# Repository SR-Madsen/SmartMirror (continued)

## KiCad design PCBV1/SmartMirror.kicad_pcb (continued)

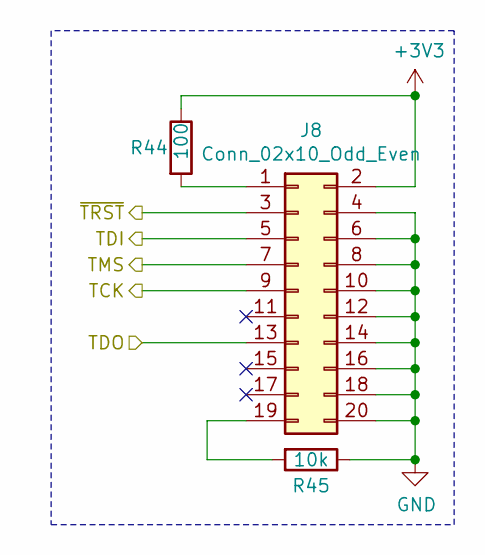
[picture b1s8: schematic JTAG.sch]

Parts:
J8: Conn_02x10_Odd_Even; PinHeader_2x10_P1.27mm_Vertical_SMD
R44: 100; R_0603_1608Metric
R45: 10k; R_0603_1608Metric

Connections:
+3V3: J8.2, R44.1; also elsewhere on the board
/Processor/JTAG_TCK: J8.9; also elsewhere on the board
/Processor/JTAG_TDI: J8.5; also elsewhere on the board
/Processor/JTAG_TDO: J8.13; also elsewhere on the board
/Processor/JTAG_TMS: J8.7; also elsewhere on the board
/Processor/~JTAG_TRST: J8.3; also elsewhere on the board
GND: J8.4, J8.6, J8.8, J8.10, J8.12, J8.14, J8.16, J8.18, J8.20, R45.1; also elsewhere on the board
unnamed: J8.1, R44.2
unnamed: J8.19, R45.2

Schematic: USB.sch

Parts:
C126: 100n; C_0603_1608Metric
C127: 10u; C_0603_1608Metric
U16: MIC2026-1BM; SOIC-8_3.9x4.9mm_P1.27mm

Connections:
+5V: C126.2, C127.2, U16.7 (IN); also elsewhere on the board
/Processor/USB1_OC: U16.2 (FLGA); also elsewhere on the board
/Processor/USB1_PWR: U16.1 (ENA); also elsewhere on the board
/Processor/USB2_OC: U16.3 (FLGB); also elsewhere on the board
/Processor/USB2_PWR: U16.4 (ENB); also elsewhere on the board
/USB/USB_VBUS1: U16.8 (OUTA); also elsewhere on the board
/USB/USB_VBUS2: U16.5 (OUTB); also elsewhere on the board
GND: C126.1, C127.1, U16.6 (GND); also elsewhere on the board

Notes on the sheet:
USB Power Distribution Switch

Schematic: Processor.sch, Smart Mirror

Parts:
C69, C71, C76, C78, C79, C81, C84, C86, C88, C89, C90, C91, C93, C94, C95, C97, C98, C100, C101, C102, C103, C106, C107, C109, C110: 220n; C_0402_1005Metric
C70, C72, C74, C77: 24p; C_0402_1005Metric
C80, C99, C104: 22µ; C_0603_1608Metric
C83, C87, C96: 10µ; C_0603_1608Metric
C85: 100n; C_0402_1005Metric
C92, C105: 4.7µ; C_0603_1608Metric
C123, C124: 1u; C_0603_1608Metric
C125: 10u; C_0402_1005Metric
R33, R34: 4.7k; R_0603_1608Metric
R35: 2.2M; R_0603_1608Metric
R36: 240R; R_0402_1005Metric
SW2: SW_DIP_x02; SW_DIP_SPSTx02_Slide_6.7x6.64mm_W6.73mm_P2.54mm_LowProfile_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
U1: MCIMX6Y2CVM08AB; Manufacturer_Part_Number MCIMX6Y2CVM08AB; Mouser Part Number 771-MCIMX6Y2CVM08AB
Y2: ECS.32712.512; ECS32712512TR
Y3: ECS2401823BJTM; ECS2401823BJTMTR

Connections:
+1V35: C69.2, C76.2, C81.2, C96.2, C97.2, C103.2, C104.1, C105.1, C106.1, C107.1, C109.2, U1.G6 (NVCC_DRAM_1), U1.H6 (NVCC_DRAM_2), U1.H9 (VDD_SOC_IN_1), U1.H10 (VDD_SOC_IN_2), U1.J6 (NVCC_DRAM_3), U1.J9 (VDD_SOC_IN_3), U1.J10 (VDD_SOC_IN_4), U1.K6 (NVCC_DRAM_4), U1.K9 (VDD_SOC_IN_5), U1.K10 (VDD_SOC_IN_6), U1.L6 (NVCC_DRAM_5), U1.M6 (NVCC_DRAM_6); also elsewhere on the board
+3V3: C71.2, C83.1, C84.1, C86.2, C87.1, C88.1, C89.1, C90.2, C91.1, C92.1, C93.1, C98.1, C110.1, R33.2, R34.2, U1.C4 (NVCC_SD1), U1.E7 (NVCC_NAND), U1.E13 (NVCC_LCD), U1.F13 (NVCC_ENET), U1.H13 (NVCC_UART), U1.J13 (NVCC_GPIO), U1.L13 (VDDA_ADC_3P3), U1.M13 (ADC_VREFH), U1.N13 (VDD_HIGH_IN), U1.P12 (VDD_SNVS_IN), U1.P13 (NVCC_PLL), U1.R14 (VDD_HIGH_CAP_1), U1.R15 (VDD_HIGH_CAP_2); also elsewhere on the board
+5V: C123.1, C124.1, U1.T12 (USB_OTG1_VBUS), U1.U12 (USB_OTG2_VBUS); also elsewhere on the board
/DDR/DDR_A0: U1.L5 (DRAM_ADDR00); also elsewhere on the board
/DDR/DDR_A1: U1.H2 (DRAM_ADDR01); also elsewhere on the board
/DDR/DDR_A2: U1.K1 (DRAM_ADDR02); also elsewhere on the board
/DDR/DDR_A3: U1.M2 (DRAM_ADDR03); also elsewhere on the board
/DDR/DDR_A4: U1.K4 (DRAM_ADDR04); also elsewhere on the board
/DDR/DDR_A5: U1.L1 (DRAM_ADDR05); also elsewhere on the board
/DDR/DDR_A6: U1.G2 (DRAM_ADDR06); also elsewhere on the board
/DDR/DDR_A7: U1.H4 (DRAM_ADDR07); also elsewhere on the board
/DDR/DDR_A8: U1.J4 (DRAM_ADDR08); also elsewhere on the board
/DDR/DDR_A9: U1.L2 (DRAM_ADDR09); also elsewhere on the board
/DDR/DDR_A10: U1.M4 (DRAM_ADDR10); also elsewhere on the board
/DDR/DDR_A11: U1.K3 (DRAM_ADDR11); also elsewhere on the board
/DDR/DDR_A12: U1.L4 (DRAM_ADDR12); also elsewhere on the board
/DDR/DDR_A13: U1.H3 (DRAM_ADDR13); also elsewhere on the board
/DDR/DDR_BA0: U1.M1 (DRAM_SDBA0); also elsewhere on the board
/DDR/DDR_BA1: U1.H1 (DRAM_SDBA1); also elsewhere on the board
/DDR/DDR_BA2: U1.K2 (DRAM_SDBA2); also elsewhere on the board
/DDR/DDR_CKE: U1.M3 (DRAM_SDCKE0); also elsewhere on the board
/DDR/DDR_CK_N: U1.P2 (DRAM_SDCLK0_N); also elsewhere on the board
/DDR/DDR_CK_P: U1.P1 (DRAM_SDCLK0_P); also elsewhere on the board
/DDR/DDR_D0: U1.T4 (DRAM_DATA00); also elsewhere on the board
/DDR/DDR_D1: U1.T8 (DRAM_DATA05); also elsewhere on the board
/DDR/DDR_D2: U1.U4 (DRAM_DATA07); also elsewhere on the board
/DDR/DDR_D3: U1.U8 (DRAM_DATA04); also elsewhere on the board
/DDR/DDR_D4: U1.T6 (DRAM_DATA02); also elsewhere on the board
/DDR/DDR_D5: U1.U7 (DRAM_DATA03); also elsewhere on the board
/DDR/DDR_D6: U1.T5 (DRAM_DATA06); also elsewhere on the board
/DDR/DDR_D7: U1.U6 (DRAM_DATA01); also elsewhere on the board
/DDR/DDR_D8: U1.U2 (DRAM_DATA08); also elsewhere on the board
/DDR/DDR_D9: U1.P5 (DRAM_DATA12); also elsewhere on the board
/DDR/DDR_D10: U1.R1 (DRAM_DATA15); also elsewhere on the board
/DDR/DDR_D11: U1.R4 (DRAM_DATA11); also elsewhere on the board
/DDR/DDR_D12: U1.P3 (DRAM_DATA13); also elsewhere on the board
/DDR/DDR_D13: U1.U5 (DRAM_DATA10); also elsewhere on the board
/DDR/DDR_D14: U1.R2 (DRAM_DATA14); also elsewhere on the board
/DDR/DDR_D15: U1.U3 (DRAM_DATA09); also elsewhere on the board
/DDR/DDR_LDM: U1.T7 (DRAM_DQM0); also elsewhere on the board
/DDR/DDR_LDQS_N: U1.P7 (DRAM_SDQS0_N); also elsewhere on the board
/DDR/DDR_LDQS_P: U1.P6 (DRAM_SDQS0_P); also elsewhere on the board
/DDR/DDR_ODT: U1.N1 (DRAM_ODT0); also elsewhere on the board
/DDR/DDR_UDM: U1.T3 (DRAM_DQM1); also elsewhere on the board
/DDR/DDR_UDQS_N: U1.T2 (DRAM_SDQS1_N); also elsewhere on the board
/DDR/DDR_UDQS_P: U1.T1 (DRAM_SDQS1_P); also elsewhere on the board
/DDR/DRAM_VREF: U1.P4 (DRAM_VREF); also elsewhere on the board
/DDR/~DDR_CAS: U1.J2 (DRAM_CAS_B); also elsewhere on the board
/DDR/~DDR_CS: U1.N2 (DRAM_CS0_B); also elsewhere on the board
/DDR/~DDR_RAS: U1.M5 (DRAM_RAS_B); also elsewhere on the board
/DDR/~DDR_WE: U1.J1 (DRAM_SDWE_B); also elsewhere on the board
/Flash/ALE: U1.B4 (NAND_ALE); also elsewhere on the board
/Flash/CLE: U1.A4 (NAND_CLE); also elsewhere on the board
/Flash/D0: U1.D7 (NAND_DATA00); also elsewhere on the board
/Flash/D1: U1.B7 (NAND_DATA01); also elsewhere on the board
/Flash/D2: U1.A7 (NAND_DATA02); also elsewhere on the board
/Flash/D3: U1.D6 (NAND_DATA03); also elsewhere on the board
/Flash/D4: U1.C6 (NAND_DATA04); also elsewhere on the board
/Flash/D5: U1.B6 (NAND_DATA05); also elsewhere on the board
/Flash/D6: U1.A6 (NAND_DATA06); also elsewhere on the board
/Flash/D7: U1.A5 (NAND_DATA07); also elsewhere on the board
/Flash/~CE: U1.C5 (NAND_CE0_B); also elsewhere on the board
/Processor/ARM_CAP: C78.1, C79.1, C80.1, U1.G9 (VDD_ARM_CAP_1), U1.G10 (VDD_ARM_CAP_2), U1.G11 (VDD_ARM_CAP_3), U1.H11 (VDD_ARM_CAP_4)
/Processor/BM0: SW2.3, U1.T10 (BOOT_MODE0)
/Processor/BM1: SW2.4, U1.U10 (BOOT_MODE1)
/Processor/DRAM_RESET: U1.G4 (DRAM_RESET); also elsewhere on the board
/Processor/ENET1_MDC: U1.C16 (ENET2_RX_DATA1); also elsewhere on the board
/Processor/ENET1_MDIO: U1.C17 (ENET2_RX_DATA0); also elsewhere on the board
/Processor/ENET1_REF_CLK: U1.F14 (ENET1_TX_CLK); also elsewhere on the board
/Processor/ENET1_RX0: U1.F16 (ENET1_RX_DATA0); also elsewhere on the board
/Processor/ENET1_RX1: U1.E17 (ENET1_RX_DATA1); also elsewhere on the board
/Processor/ENET1_RX_EN: U1.E16 (ENET1_RX_EN); also elsewhere on the board
/Processor/ENET1_RX_ER: U1.D15 (ENET1_RX_ER); also elsewhere on the board
/Processor/ENET1_TX0: U1.E15 (ENET1_TX_DATA0); also elsewhere on the board
/Processor/ENET1_TX1: U1.E14 (ENET1_TX_DATA1); also elsewhere on the board
/Processor/ENET1_TX_EN: U1.F15 (ENET1_TX_EN); also elsewhere on the board
/Processor/JTAG_TCK: U1.M14 (JTAG_TCK); also elsewhere on the board
/Processor/JTAG_TDI: U1.N16 (JTAG_TDI); also elsewhere on the board
/Processor/JTAG_TDO: U1.N15 (JTAG_TDO); also elsewhere on the board
/Processor/JTAG_TMS: U1.P14 (JTAG_TMS); also elsewhere on the board
/Processor/LCD_RESET: U1.E9 (LCD_RESET); also elsewhere on the board
/Processor/LCD_VSYNC: U1.C9 (LCD_VSYNC); also elsewhere on the board
/Processor/SD1_CLK: U1.C1 (SD1_CLK); also elsewhere on the board
/Processor/SD1_CMD: U1.C2 (SD1_CMD); also elsewhere on the board
/Processor/SD1_D0: U1.B3 (SD1_DATA0); also elsewhere on the board
/Processor/SD1_D1: U1.B2 (SD1_DATA1); also elsewhere on the board
/Processor/SD1_D2: U1.B1 (SD1_DATA2); also elsewhere on the board
/Processor/SD1_D3: U1.A2 (SD1_DATA3); also elsewhere on the board
/Processor/SD2_CLK: U1.F2 (CSI_VSYNC); also elsewhere on the board
/Processor/SD2_CMD: U1.F3 (CSI_HSYNC); also elsewhere on the board
/Processor/SD2_D0: U1.E4 (CSI_DATA00); also elsewhere on the board
/Processor/SD2_D1: U1.E3 (CSI_DATA01); also elsewhere on the board
/Processor/SD2_D2: U1.E2 (CSI_DATA02); also elsewhere on the board
/Processor/SD2_D3: U1.E1 (CSI_DATA03); also elsewhere on the board
/Processor/SOC_CAP: C99.1, C100.1, C101.1, C102.1, U1.G8 (VDD_SOC_CAP_1), U1.H8 (VDD_SOC_CAP_2), U1.J8 (VDD_SOC_CAP_3), U1.J11 (VDD_SOC_CAP_4), U1.K8 (VDD_SOC_CAP_5), U1.K11 (VDD_SOC_CAP_6), U1.L8 (VDD_SOC_CAP_7), U1.L9 (VDD_SOC_CAP_8), U1.L10 (VDD_SOC_CAP_9), U1.L11 (VDD_SOC_CAP_10)
/Processor/USB1D_N: U1.T15 (USB_OTG1_DN); also elsewhere on the board
/Processor/USB1D_P: U1.U15 (USB_OTG1_DP); also elsewhere on the board
/Processor/USB1_OC: U1.L15 (GPIO1_IO01); also elsewhere on the board
/Processor/USB1_PWR: U1.M16 (GPIO1_IO04); also elsewhere on the board
/Processor/USB2D_N: U1.T13 (USB_OTG2_DN); also elsewhere on the board
/Processor/USB2D_P: U1.U13 (USB_OTG2_DP); also elsewhere on the board
/Processor/USB2_ID: U1.M17 (GPIO1_IO05); also elsewhere on the board
/Processor/USB2_OC: U1.L17 (GPIO1_IO03); also elsewhere on the board
/Processor/USB2_PWR: U1.L14 (GPIO1_IO02); also elsewhere on the board
/Processor/~JTAG_TRST: U1.N14 (JTAG_TRST_B); also elsewhere on the board
/Processor/~NAND_RDY: U1.A3 (NAND_READY_B); also elsewhere on the board
/Processor/~NAND_RE: U1.D8 (NAND_RE_B); also elsewhere on the board
/Processor/~NAND_WE: U1.C8 (NAND_WE_B); also elsewhere on the board
/Processor/~NAND_WP: U1.D5 (NAND_WP_B); also elsewhere on the board
/Processor/~SD1_CD: U1.D3 (CSI_DATA05); also elsewhere on the board
/UART/CTS: U1.J14 (UART1_RTS_B); also elsewhere on the board
/UART/RTS: U1.K15 (UART1_CTS_B); also elsewhere on the board
/UART/RX: U1.K14 (UART1_TX_DATA); also elsewhere on the board
/UART/TX: U1.K16 (UART1_RX_DATA); also elsewhere on the board
/Video/CLK: U1.A8 (LCD_CLK); also elsewhere on the board
/Video/DATA00: U1.B9 (LCD_DATA00); also elsewhere on the board
/Video/DATA01: U1.A9 (LCD_DATA01); also elsewhere on the board
/Video/DATA02: U1.E10 (LCD_DATA02); also elsewhere on the board
/Video/DATA03: U1.D10 (LCD_DATA03); also elsewhere on the board
/Video/DATA04: U1.C10 (LCD_DATA04); also elsewhere on the board
/Video/DATA05: U1.B10 (LCD_DATA05); also elsewhere on the board
/Video/DATA06: U1.A10 (LCD_DATA06); also elsewhere on the board
/Video/DATA07: U1.D11 (LCD_DATA07); also elsewhere on the board
/Video/DATA08: U1.B11 (LCD_DATA08); also elsewhere on the board
/Video/DATA09: U1.A11 (LCD_DATA09); also elsewhere on the board
/Video/DATA10: U1.E12 (LCD_DATA10); also elsewhere on the board
/Video/DATA11: U1.D12 (LCD_DATA11); also elsewhere on the board
/Video/DATA12: U1.C12 (LCD_DATA12); also elsewhere on the board
/Video/DATA13: U1.B12 (LCD_DATA13); also elsewhere on the board
/Video/DATA14: U1.A12 (LCD_DATA14); also elsewhere on the board
/Video/DATA15: U1.D13 (LCD_DATA15); also elsewhere on the board
/Video/DATA16: U1.C13 (LCD_DATA16); also elsewhere on the board
/Video/DATA17: U1.B13 (LCD_DATA17); also elsewhere on the board
/Video/DATA18: U1.A13 (LCD_DATA18); also elsewhere on the board
/Video/DATA19: U1.D14 (LCD_DATA19); also elsewhere on the board
/Video/DATA20: U1.C14 (LCD_DATA20); also elsewhere on the board
/Video/DATA21: U1.B14 (LCD_DATA21); also elsewhere on the board
/Video/DATA22: U1.A14 (LCD_DATA22); also elsewhere on the board
/Video/DATA23: U1.B16 (LCD_DATA23); also elsewhere on the board
/Video/ENABLE: U1.B8 (LCD_ENABLE); also elsewhere on the board
/Video/HSYNC: U1.D9 (LCD_HSYNC); also elsewhere on the board
GND: C69.1, C70.2, C71.1, C72.2, C74.2, C76.1, C77.2, C78.2, C79.2, C80.2, C81.1, C83.2, C84.2, C85.2, C86.1, C87.2, C88.2, C89.2, C90.1, C91.2, C92.2, C93.2, C94.2, C95.2, C96.1, C97.1, C98.2, C99.2, C100.2, C101.2, C102.2, C103.1, C104.2, C105.2, C106.2, C107.2, C109.1, C110.2, C123.2, C124.2, C125.2, R35.2, R36.1, U1.A1 (VSS_1), U1.A17 (VSS_2), U1.C3 (VSS_3), U1.C7 (VSS_4), U1.C11 (VSS_5), U1.C15 (VSS_6), U1.E8 (VSS_7), U1.E11 (VSS_8), U1.F6 (VSS_9), U1.F7 (VSS_10), U1.F8 (VSS_11), U1.F9 (VSS_12), U1.F10 (VSS_13), U1.F11 (VSS_14), U1.F12 (VSS_15), U1.G3 (VSS_16), U1.G5 (VSS_17), U1.G7 (VSS_18), U1.G12 (VSS_19), U1.G15 (VSS_20), U1.H7 (VSS_21), U1.H12 (VSS_22), U1.J5 (VSS_23), U1.J7 (VSS_24), U1.J12 (VSS_25), U1.K7 (VSS_26), U1.K12 (VSS_27), U1.L3 (VSS_28), U1.L7 (VSS_29), U1.L12 (VSS_30), U1.M7 (VSS_31), U1.M8 (VSS_32), U1.M9 (VSS_33), U1.M10 (VSS_34), U1.M11 (VSS_35), U1.M12 (NGND_KEL0), U1.N3 (VSS_36), U1.N5 (VSS_37), U1.N7 (TEST_MODE), U1.P15 (JTAG_MOD), U1.R3 (VSS_38), U1.R5 (VSS_39), U1.R7 (VSS_40), U1.R11 (VSS_41), U1.R16 (VSS_42), U1.R17 (VSS_43), U1.T14 (VSS_44), U1.U1 (VSS_45), U1.U14 (VSS_46), U1.U17 (VSS_47), Y3.2, Y3.4; also elsewhere on the board
unnamed: C70.1, U1.U11 (RTC_XTALO), Y2.1
unnamed: C72.1, U1.T11 (RTC_XTALI), Y2.2
unnamed: C74.1, U1.T17 (XTALO), Y3.1
unnamed: C77.1, R35.1, U1.T16 (XTALI), Y3.3
unnamed: C94.1, U1.N12 (VDD_SNVS_CAP)
unnamed: C95.1, U1.N6 (NVCC_DRAM_2P5)
unnamed: C85.1, C125.1, U1.R12 (VDD_USB_CAP)
unnamed: R33.1, SW2.1
unnamed: R34.1, SW2.2
unnamed: R36.2, U1.N4 (DRAM_ZQPAD)

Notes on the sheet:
Boot mode switches
00: Boot from fuses 01: Serial downloader 10: Internal boot 11: Reserver
Place resistor close to XTALI

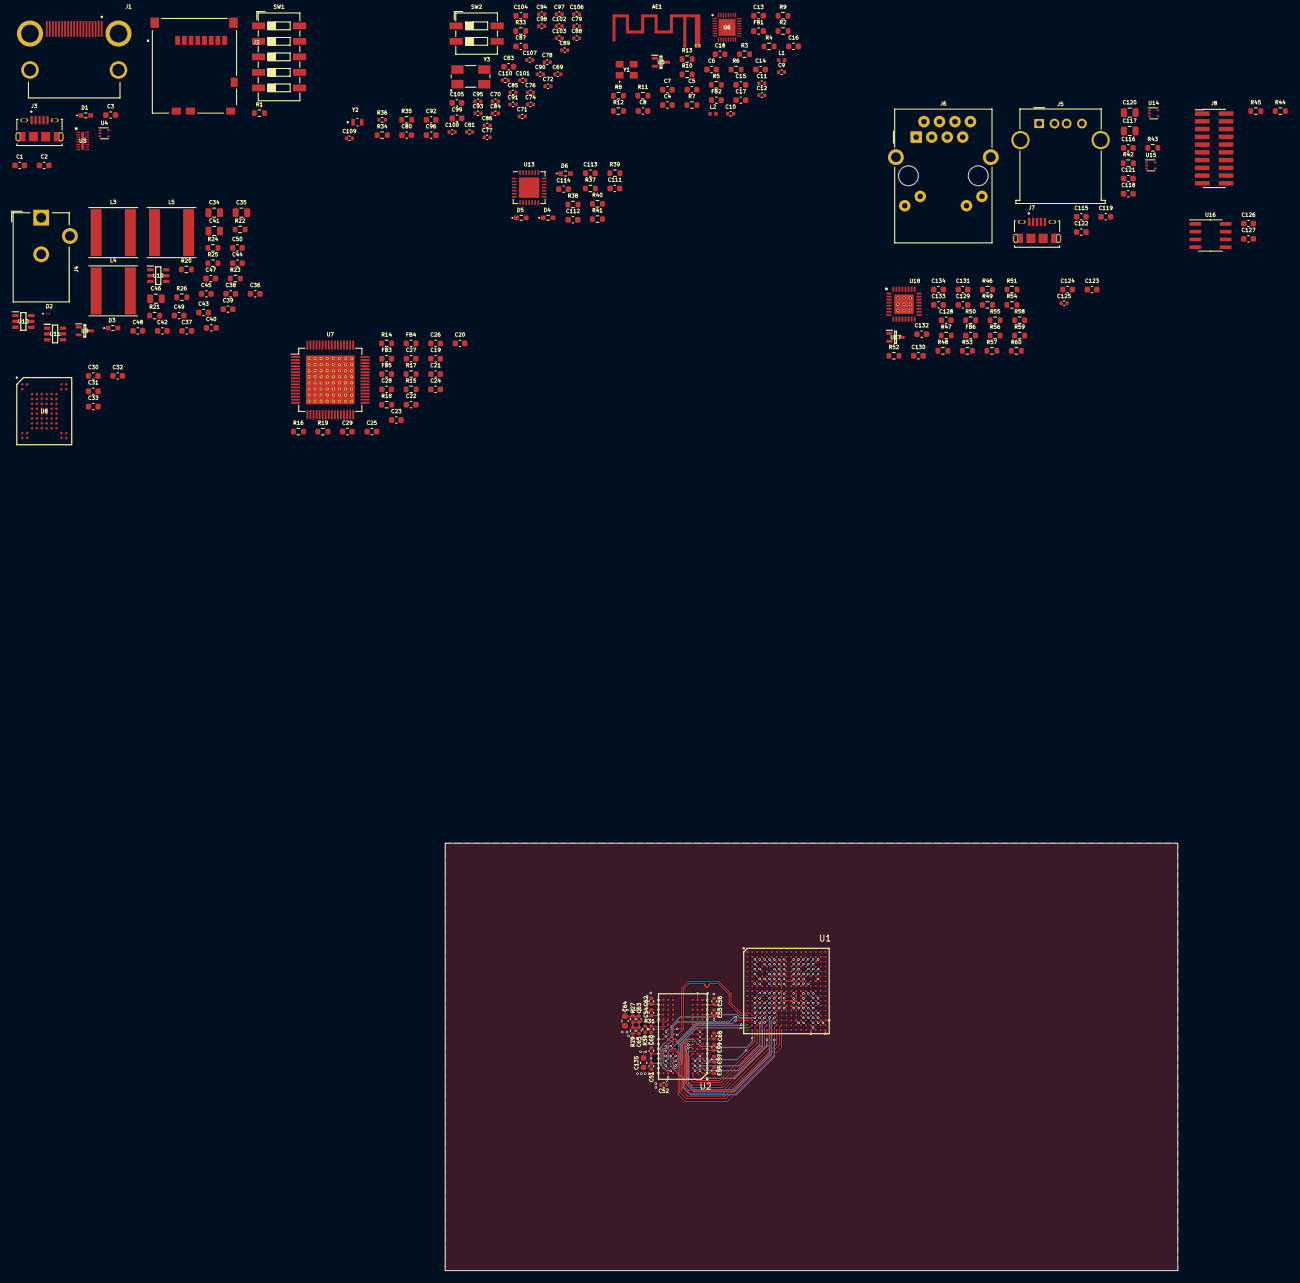
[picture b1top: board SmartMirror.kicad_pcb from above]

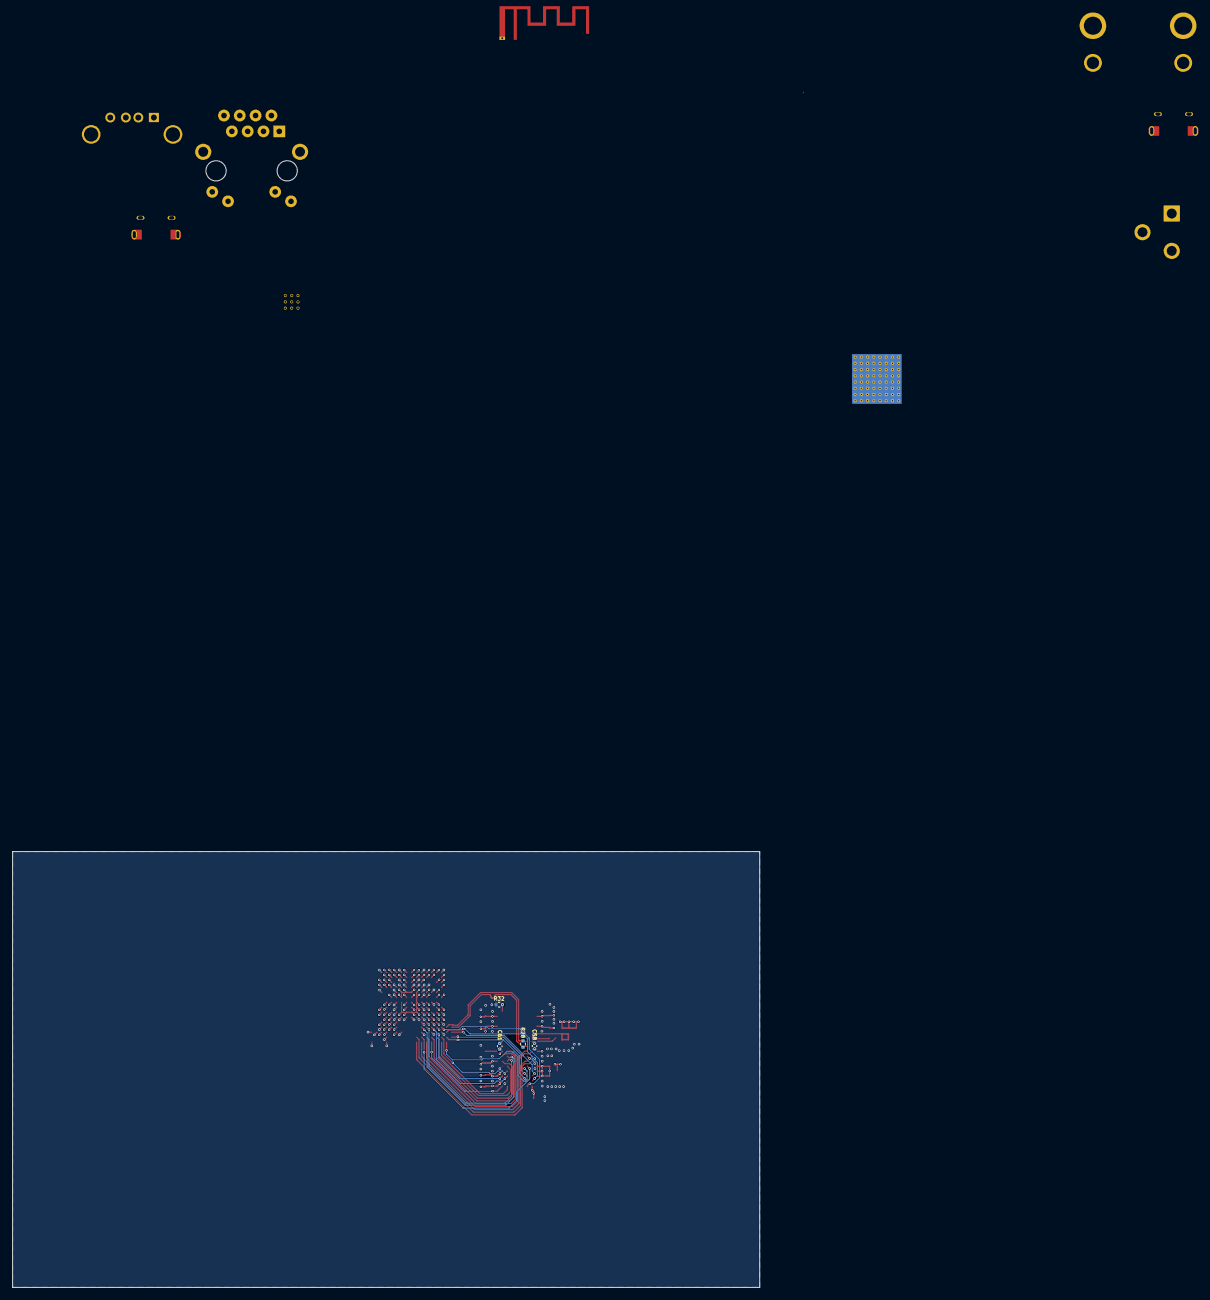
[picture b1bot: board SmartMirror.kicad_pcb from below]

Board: 4 copper layers, 120.0 x 70.0 mm, 238 parts (4 on the bottom side), 240 nets.

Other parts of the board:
C128, C130, C131, C133: 100n; C_0603_1608Metric
C129, C132: 22u; C_0603_1608Metric
C134: 2.2u; C_0603_1608Metric
FB6: 600R; L_0603_1608Metric
R46, R47, R50, R51, R53, R54, R55, R58, R59: 1k; R_0603_1608Metric
R48: 6.49k; R_0603_1608Metric
R49, R52, R56, R57, R60: 4.7k; R_0603_1608Metric
U17: MCP112T-315E_LB; MCP112T-315E-LB
U18: KSZ8081RNB

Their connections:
+3V3: C128.1, C129.1, C130.1, FB6.2, R46.1, R47.1, R49.1, R52.1, R56.1, R57.1, R60.1, U17.3, U18.17; also elsewhere on the board
/Ethernet/CAST_OFF: R59.2, U18.19
/Ethernet/CONFIG0: R52.2, U18.28
/Ethernet/CONFIG1: R53.2, U18.29
/Ethernet/ETH_RX_N: U18.4; also elsewhere on the board
/Ethernet/ETH_RX_P: U18.5; also elsewhere on the board
/Ethernet/ETH_TX_N: U18.6; also elsewhere on the board
/Ethernet/ETH_TX_P: U18.7; also elsewhere on the board
/Ethernet/LED0: R56.2, U18.30; also elsewhere on the board
/Ethernet/LED1: R57.2, U18.31; also elsewhere on the board
/Ethernet/NAND_TREE: R60.2, U18.21
/Ethernet/PHYAD0: R49.2, U18.13
/Ethernet/PHYAD1: R50.2, U18.14
/Ethernet/~RESET: U17.1, U18.32
/Processor/ENET1_MDC: R46.2, U18.12; also elsewhere on the board
/Processor/ENET1_MDIO: R47.2, U18.11; also elsewhere on the board
/Processor/ENET1_REF_CLK: U18.9; also elsewhere on the board
/Processor/ENET1_RX0: R58.2, U18.16; also elsewhere on the board
/Processor/ENET1_RX1: R51.2, U18.15; also elsewhere on the board
/Processor/ENET1_RX_EN: R54.2, U18.18; also elsewhere on the board
/Processor/ENET1_RX_ER: R55.2, U18.20; also elsewhere on the board
/Processor/ENET1_TX0: U18.24; also elsewhere on the board
/Processor/ENET1_TX1: U18.25; also elsewhere on the board
/Processor/ENET1_TX_EN: U18.23; also elsewhere on the board
GND: C128.2, C129.2, C130.2, C131.1, C132.1, C133.1, C134.1, R48.1, R50.1, R51.1, R53.1, R54.1, R55.1, R58.1, R59.1, U17.2, U18.1, U18.33; also elsewhere on the board
unnamed: C131.2, C132.2, FB6.1, U18.3
unnamed: C133.2, C134.2, U18.2
unnamed: R48.2, U18.10

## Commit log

2021-01-21 First setup of KiCad schematics. Added microprocessor documentation.
2021-01-28 Assigned pins in NXP configuration tool to .mex file.
2021-02-08 Added documentation of general design layout and Embedded Linux.
2021-02-15 Added schematic for power through barrel jack and voltage converters, connected DRAM.
2021-02-16 Changes to DDR schematic.
2021-04-07 Made comments and some circuits.
2021-08-16 Made a bunch of very small changes.
2022-04-21 Added UART, modifications to video etc.
2022-04-21 Minor adjustments with video connections.
2022-04-21 Finished video signals, added HDMI and SD connectors.
2022-04-23 Merge of recent changes to default master (#2)
    * Made a bunch of very small changes.
    * Added UART, modifications to video etc.
    * Minor adjustments with video connections.
    * Finished video signals, added HDMI and SD connectors.
2022-04-23 Added SD filter and USB-to-UART IC.
2022-04-23 Merge of forgotten changes (#3)
    * Added SD filter and USB-to-UART IC.
2022-04-23 Changed note.
2022-05-02 Added documentation.
2022-05-05 Many minor changes to component footprints and schematics.
2022-05-06 Added NAND flash with connections, updated IO config.
2022-05-11 Laid final hands on Wi-Fi and all circuits. Started work on PCB.
2022-05-12 Added JTAG, USB OTG, USB Host, and Ethernet.
2022-05-17 Many changes to footprints (0603 -> 0402), basic DDR layout set, no traces made.
2022-06-01 Routing of DDR. Not finished.
